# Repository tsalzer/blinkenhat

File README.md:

# BlinkenHat

This is a project to enable people with limited knowledge in electronics or programming to build fancy flashing LED accessiors.

The documentation can be found at [blinkenhat.org](https://blinkenhat.org).

## Releases

### v0.5: First public release

This is basically the release that was distributed with the first version of the workshop.

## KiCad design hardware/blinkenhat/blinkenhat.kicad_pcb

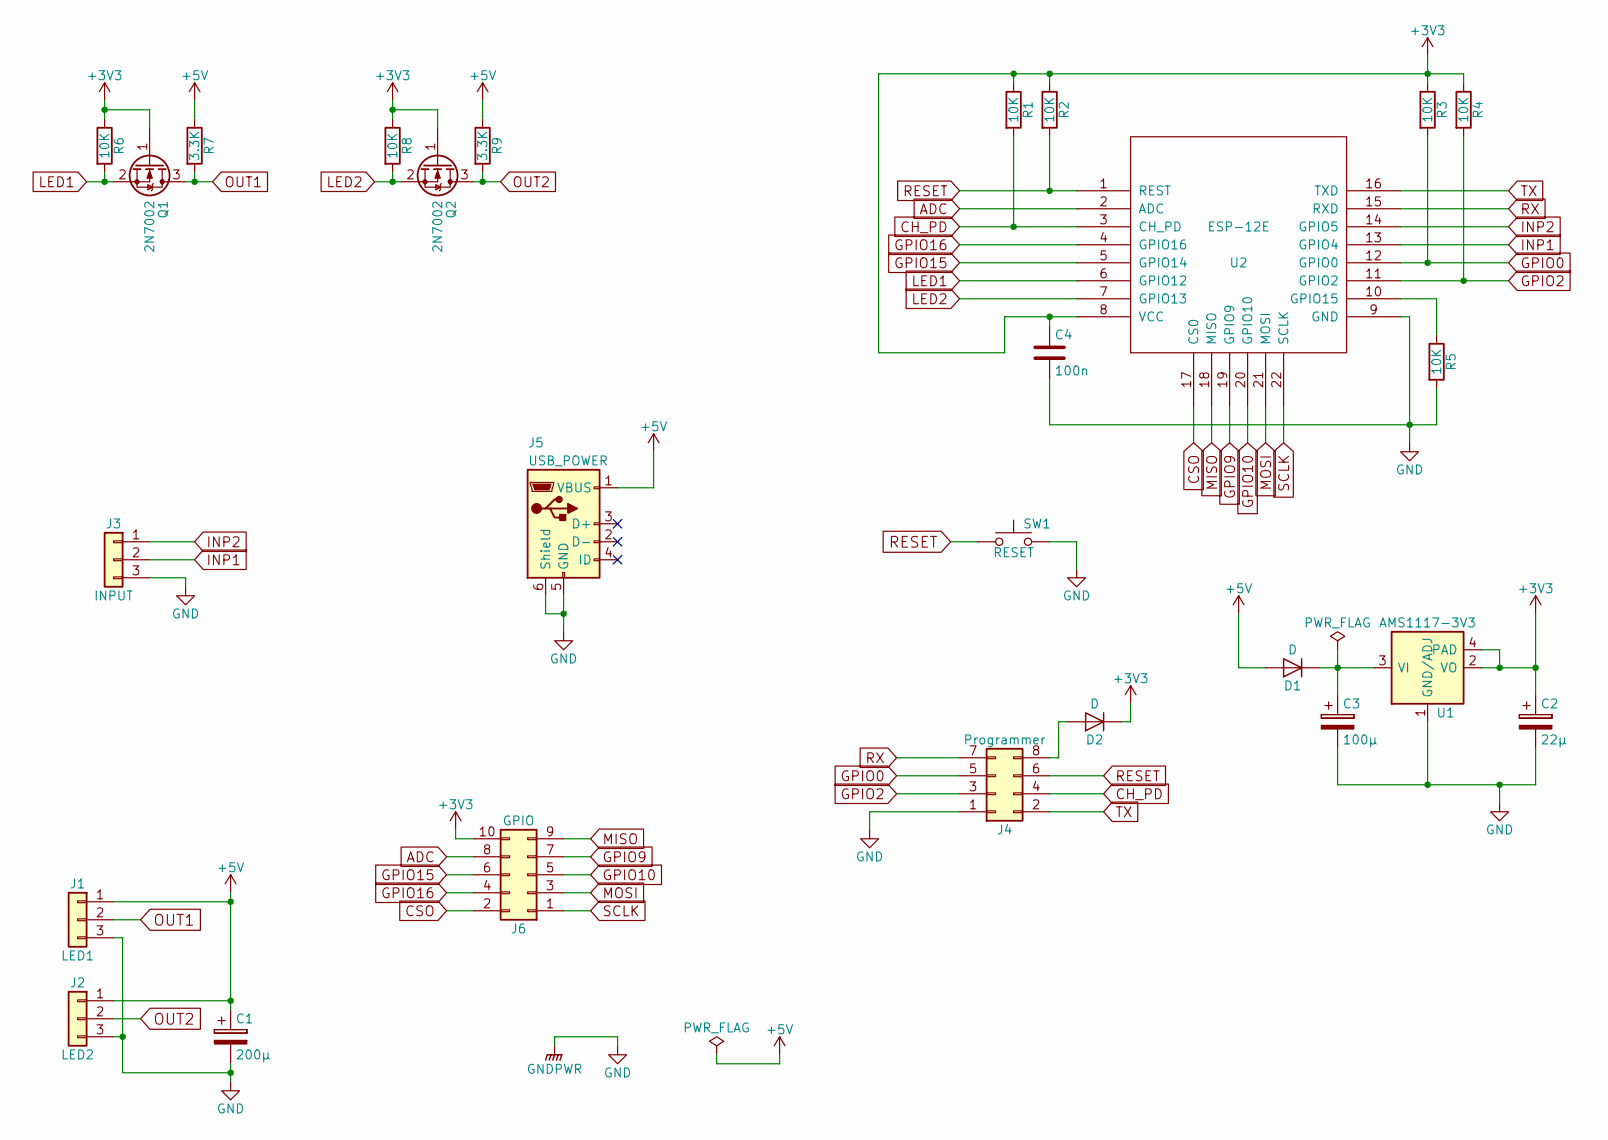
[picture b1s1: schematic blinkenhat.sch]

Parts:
C1: 200µ; CP_Tantalum_Case-C_EIA-6032-28_Reflow
C2: 22µ; CP_Tantalum_Case-B_EIA-3528-21_Reflow
C3: 100µ; CP_Tantalum_Case-C_EIA-6032-28_Reflow
C4: 100n; C_0603
D1, D2: D; DO-214AC(SMA)
J1: LED1; JST_XH_B03B-XH-A_03x2.50mm_Straight
J2: LED2; JST_XH_B03B-XH-A_03x2.50mm_Straight
J3: INPUT; JST_XH_B03B-XH-A_03x2.50mm_Straight
J4: Programmer; Pin_Header_Straight_2x04_Pitch2.54mm
J5: USB_POWER; USB_Micro-B_10103594-0001LF
J6: GPIO; Pin_Header_Straight_2x05_Pitch1.27mm
Q1, Q2: 2N7002; SOT-23
R1, R2, R3, R4, R5, R6, R8: 10K; R_0603
R7, R9: 3.3K; R_0603
SW1: RESET; SW_SPST_PTS645
U1: AMS1117-3V3; SOT-223; MPN LM1117
U2: ESP-12E; MPN ESP-12E

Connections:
+3V3: C2.1, C4.1, D2.1 (K), J6.10, Q1.1 (G), Q2.1 (G), R1.1, R2.1, R3.1, R4.1, R6.1, R8.1, U1.2 (VO), U1.4 (PAD), U2.8 (VCC)
+5V: C1.1, D1.2 (A), J1.1, J2.1, J5.1 (VBUS), R7.1, R9.1
ADC: J6.8, U2.2 (ADC)
CH_PD: J4.4, R1.2, U2.3 (CH_PD)
CSO: J6.2, U2.17 (CS0)
GND: C1.2, C2.2, C3.2, C4.2, J1.3, J2.3, J3.3, J4.1, J5.5 (GND), J5.6 (Shield), R5.2, SW1.2, U1.1 (GND/ADJ), U2.9 (GND)
GPIO0: J4.5, R3.2, U2.12 (GPIO0)
GPIO2: J4.3, R4.2, U2.11 (GPIO2)
GPIO9: J6.7, U2.19 (GPIO9)
GPIO10: J6.5, U2.20 (GPIO10)
GPIO15: J6.6, U2.5 (GPIO14)
GPIO16: J6.4, U2.4 (GPIO16)
INP1: J3.2, U2.13 (GPIO4)
INP2: J3.1, U2.14 (GPIO5)
LED1: Q1.2 (S), R6.2, U2.6 (GPIO12)
LED2: Q2.2 (S), R8.2, U2.7 (GPIO13)
MISO: J6.9, U2.18 (MISO)
MOSI: J6.3, U2.21 (MOSI)
unnamed: C3.1, D1.1 (K), U1.3 (VI)
unnamed: D2.2 (A), J4.8
unnamed: R5.1, U2.10 (GPIO15)
OUT1: J1.2, Q1.3 (D), R7.2
OUT2: J2.2, Q2.3 (D), R9.2
RESET: J4.6, R2.2, SW1.1, U2.1 (REST)
RX: J4.7, U2.15 (RXD)
SCLK: J6.1, U2.22 (SCLK)
TX: J4.2, U2.16 (TXD)

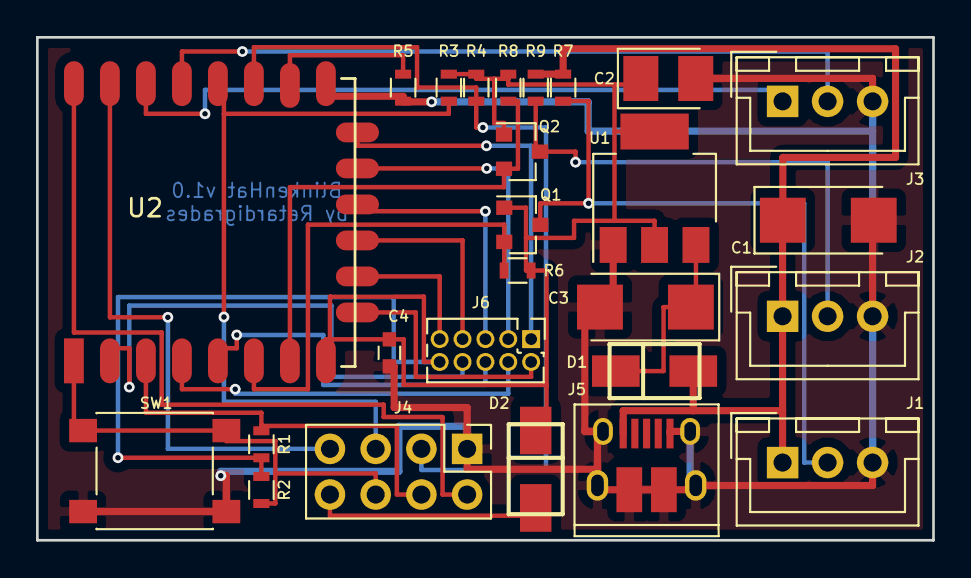
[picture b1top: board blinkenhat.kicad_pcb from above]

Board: 2 copper layers, 49.8 x 27.9 mm, 26 parts (0 on the bottom side), 27 nets.

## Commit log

2018-01-02 Setup project structure.
2018-01-03 Hardware: add kicad project.
2018-01-04 Hardware: add libraries for AMS1117 and ESP8266-12e
2018-01-04 Hardware: first version of schematic.
2018-01-04 Hardware: add library search path for kicad.
2018-01-04 Hardware: add kicad-library from thingtronics.com
2018-01-04 Hardware: add lib for diodes.
2018-01-04 Hardware: add Metadata to schematics
2018-01-04 Hardware: add generated netlist.
2018-01-04 Hardware: update schematics names.
2018-01-04 Hardware: add local symbol cache.
2018-01-04 Hardware: add generated Bill of materials.
2018-01-04 Hardware: add footprint lib table.
2018-01-04 Hardware: update project file.
2018-01-04 Hardware: add pdf plot of schematic.
2018-01-05 Hardware: regenerate Netlist.
2018-01-05 Hardware: update schematic pdf plot.
2018-01-05 Hardware: Add GPIO Header to schematic.
2018-01-05 Hardware: add pcb file.
2018-01-05 Hardware: update schematics plot.
2018-01-05 Hardware: update netlist.
2018-01-05 Hardware: another schematics update.
2018-01-05 Hardware: rotate GPIO connector.
2018-01-05 Hardware: flip programmer connector.
2018-01-05 Hardware: add generated 3d images of the Hardware.
2018-01-05 Hardware: update schematic plot.
2018-01-05 Hardware: update schematics.
2018-01-05 Hardware: change capacitors vor 3V3.
2018-01-05 Hardware: regenerate schematic plot.
2018-01-05 Hardware: redesign PCB.
2018-01-05 Hardware: update 3d images of pcb.
2018-01-11 Hardware: fix wrong connection of heat pad for AMS
2018-01-11 Hardware: fix AMS pad connection.
2018-01-17 add LED strip
2018-01-17 only update elapsed time after actually update LEDs
2018-01-17 add FastLED
2018-01-19 don't use template
2018-01-19 add first effect tests
2018-01-23 Hardware: adjust with reality.
2018-01-23 Hardware: regenerate schematic pdf.
2018-01-24 Add scrupt for default config integration.
    It creates a C header file with the contents of the default config as a
    define.
2018-01-24 Integrate default config creaion in the build process
2018-01-24 Add ArfuinoJson as a dependency
2018-01-24 Add a very simple config implementation
2018-01-24 Add generated default config to gitignore.
2018-01-24 Refactor current code based on last meeting.
    This changes the effect implementation to have a common configuration
    method, remove the reference to the LED-Band (they only need it in their
    update method), makes them independend from the framerate, call the led
    update explicit, changes the way the data is handled, etc.
2018-01-25 Test and tune dot effect.
2018-01-25 Make dot effect partially applicable.
2018-01-25 Blank leds outside of effect.
2018-01-25 Consistent camel case.
2018-01-25 Code format.
2018-01-25 Make rainbow rork on strip parts.
2018-01-25 Consistent header naming
2018-01-25 Put rainbow config in c file.
2018-01-25 Add an EffectStack for handling multiple effects.
    The EffectStack is a container to apply multiple effects to a channel.
    It is populated by the configuration.
2018-01-25 Fix rainbow effect.
2018-01-25 Format.
2018-01-25 Make effect stackable.
2018-01-25 Remove debug outpur
2018-01-25 Add gamma correction support.
2018-01-26 Introduce LEDDevice.
    The LEDDevice is the main object for controlling all LED related stuff.
    It creats the LEDBands out of the configuration and fills the Effect
    stacks for each channel. It is also responsible for initializing the
    FastLED buffers and writing thm out to the Hardware.
2018-01-26 Add travis buldfile.
2018-01-26 Install FastFEL from the lib manager
2018-01-26 Put the config in its own lib.
2018-01-26 Put LED stuff in its own lib.
2018-01-26 Give effects its own lib.
2018-01-26 Split LEDBand and LEDDevice libs.
2018-01-26 Add .ycm_extra_conf.py for easier vim usage.
2018-01-26 Implement config persistence.
2018-01-26 Add prototype for webserver
2018-01-26 Add WifiHandler prototype
2018-01-26 Add missing values to default config
2018-01-26 Integrate WebserveIntegrate Webserver
2018-01-26 Put piolibseps in ycm_extra_conf.py
2018-01-26 Integrate WifiHandler.
2018-01-26 Append chipId to wifi ssid.
2018-01-26 Give AP config a proper default.
2018-01-29 Make WebServer work.
2018-01-29 Fix config load/reload.
2018-01-29 Fix copy/paste error
2018-01-29 Longer wait for STA mode wifi
2018-01-29 Actually set up the wifi connection.
2018-01-29 Fix default config generation.
2018-01-29 Make the loop of LEDDevice nonblocking.
    We need to manually call show() of FastLED, as we may need to handle
    HTTP requests between the dither steps.
2018-01-29 Exclude backup and swap files.
2018-01-29 Reconfigure LEDDevice on config reload.
2018-01-29 Do not redraw and update in the same loop.
2018-01-29 Start webapp
2018-01-29 Add editorconfig
2018-01-29 Add basic webpack
2018-01-29 dd .babelrc
2018-01-29 Add react.
2018-01-30 change name of Config header
    the name Config.h is clashing with some other header, so we change is to something
    unique.
2018-01-31 Allow LEDs to settle.
2018-02-01 Frontend: Add basic webapp structure
2018-02-01 Frontend: add firmware update.
2018-02-01 Add script to create wbui
2018-02-01 Integrate web-ui script in build
2018-02-01 Add first version of precompiled header.
2018-02-01 Integrate compiled frontend in webserver.
2018-02-01 Frontend: Make firmware upgrade work.
2018-02-01 Update precompiled header
2018-02-01 Remove accidentially added file.
2018-02-01 Add web build to travis
2018-02-01 Frontend: Wifi-settings and style
2018-02-01 Webfrontend: Use json-server for dummy backend.
2018-02-01 Frontend: write some documentation about the dev process.
2018-02-01 fix typos
2018-02-01 fix reconnection issue after reset
    Wifi.disconnect(true);
    disconnects and erases ssid and password to clear the states for new connect
2018-02-02 increase the connection time
    after hard reset my board connects to my wifi after 2,5s
    after soft reset it takes even 4,8s to reconnect
2018-02-02 disable LED update when in AP mode and clients are connected
    When we use LED update with interrupts disabled
    the AP mode isn't working properly.
2018-02-02 Status message on save
2018-02-02 Frontend: Split out page layout.
2018-02-02 Frontend: load/save config.
2018-02-02 Frontend: General settings and Slider.
2018-02-02 Frontend: style.
2018-02-02 Frontend: Use int types for int.
2018-02-02 Frontend: basic channel config.
2018-02-02 Fronend: Add basic Effect Support.
2018-02-02 Frontend: make effects change work.
2018-02-02 Update generated frontend header.
2018-02-03 Add an index to the effects
2018-02-03 Fix web build script
2018-02-03 fix last commit
2018-02-03 Frontend: Add index to dummy.json
2018-02-03 Frontend: add effect menu to add effect.
2018-02-03 Update the web header.
2018-02-03 Wait only 5 sek for sta connect.
2018-02-03 Update LEDs only once a frame and disable dithering.
2018-02-03 use only AP mode
2018-02-03 don't stall LED when using wifi
2018-02-03 Frontend: allow less LEDs.
2018-02-03 Print Chipid on boot.
2018-02-03 Update generated header with the frontend.
2018-02-06 Add json-server to npm-run
    Running the JSON server for tests can be simplified by adding an entry
    to scripts in package.json. Add the run script, and update the README.
2018-02-08 Fix minor syntax error in webpack.config.js
    Add the missing ";".
2018-02-08 Add missing uglifyjs-webpack-plugin dependency
    The uglifyjs-webpack-plugin is used in webpack, but not declared in
    package.json, which causes IDEA to frown upon it.
2018-02-10 Add README files.
2018-02-10 Set theme jekyll-theme-cayman
2018-02-10 Create CNAME
2018-02-10 Releases via travis
2018-02-10 Do not clean before deploy
2018-02-10 Add firmware version in the wevserver /virmware ep.
2018-02-10 First public release.
2018-02-10 Add hardware doc
2018-02-13 Point to the documentation.
2018-02-13 Add some more documentation.
2018-02-13 Add a title to doc.
2018-02-13 Explain how to build the electronics.
2018-02-13 Typo.
